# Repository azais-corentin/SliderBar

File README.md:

<p align="center">

  <h3 align="center">SliderBar</h3>

  <p align="center">
    Motorized keyboard slider with an advanced controller.
  </p>
</p>

## Table of contents

- [What's that](#whats-that)
- [Quick start](#quick-start)
- [Documentation](#documentation)
- [Copyright and license](#copyright-and-license)

## What's that

It's a keyboard slider that connects to your computer using USB.
Depending on the plugins you loaded using the desktop application, you can use your slider to execute some actions.
Here are some examples:
- Switch chrome tabs easily in one swipe.
- Switch between opened applications.
- Scroll through a window.
- Control sliders and other things in applications like Photoshop or After Effects.

## Quick start

### Get started as a user

Too early in the development for that.

### Get started with development

Follow this short guide:

- Clone the repo: `git clone --recursive https://github.com/haellsigh/SliderBar.git`
- If you want to develop for desktop:
  - Install Qt Creator with Qt > 4.0
- If you want to develop for embedded:
  - Install [PlatformIO](https://platformio.org/platformio-ide) for [VSCode](https://code.visualstudio.com/) or [Atom](https://atom.io/).

Read the [Getting started page](https://sliderbar.readthedocs.io/en/latest/) for information on the SliderBar, example plugins and more.

## Documentation

SliderBar's documentation, included in this repo in the `docs/` directory, is built
with [Sphinx](http://www.sphinx-doc.org/en/master/) and
[Doxygen](http://www.doxygen.nl/) and publicly hosted ReadTheDocs at <https://sliderbar.readthedocs.io/en/latest/>.

## Copyright and license

Code and documentation copyright 2017-2018
[Haellsigh](https://github.com/haellsigh). Code and
docs released under the [MIT
License](https://github.com/Haellsigh/SliderBar/blob/master/LICENSE).

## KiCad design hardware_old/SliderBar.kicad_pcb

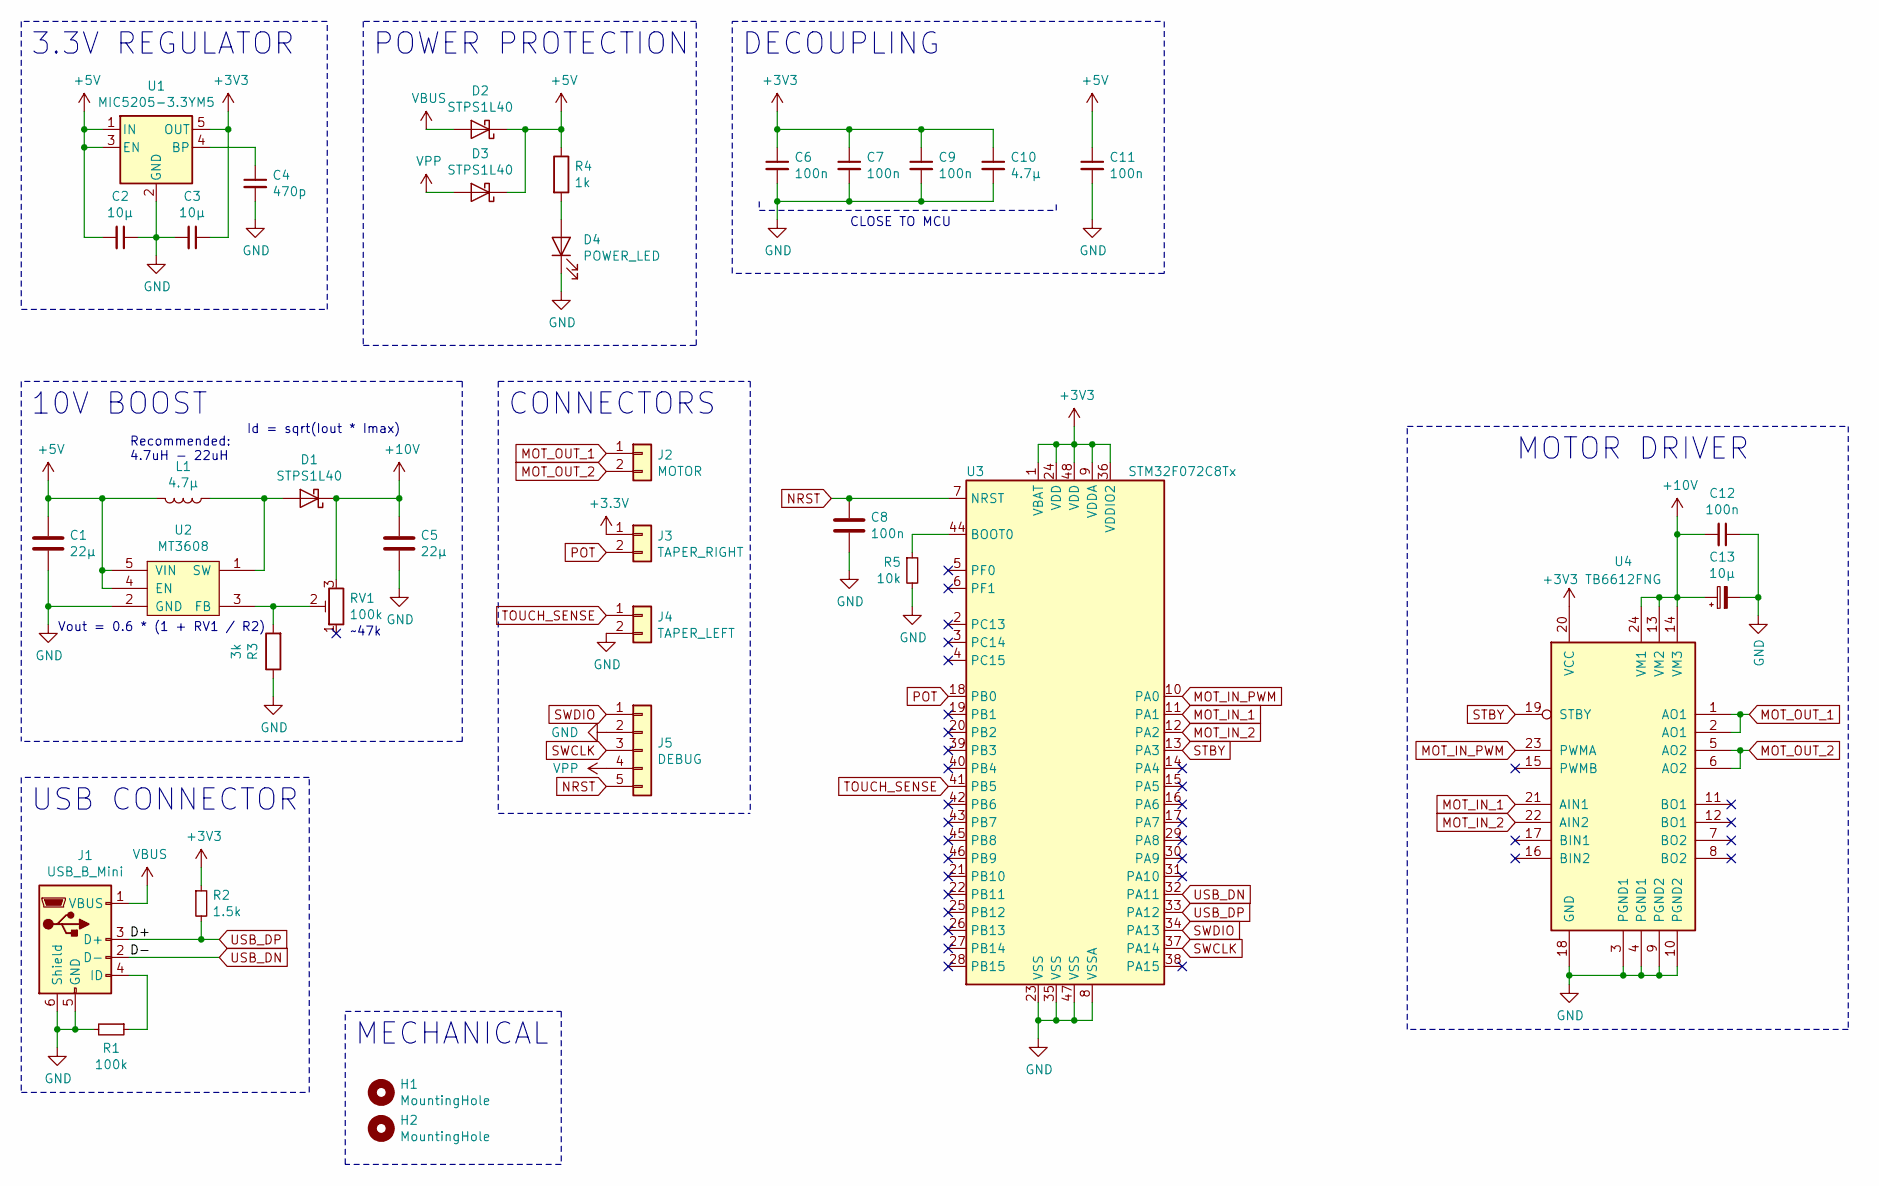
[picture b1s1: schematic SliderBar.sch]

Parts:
C1, C5: 22µ; C_0805_2012Metric_Pad1.15x1.40mm_HandSolder
C2, C3: 10µ; C_0805_2012Metric_Pad1.15x1.40mm_HandSolder
C4: 470p; C_0805_2012Metric_Pad1.15x1.40mm_HandSolder
C6, C7, C8, C9, C11, C12: 100n; C_0805_2012Metric_Pad1.15x1.40mm_HandSolder
C10: 4.7µ; C_0805_2012Metric_Pad1.15x1.40mm_HandSolder
C13: 10µ; CP_EIA-6032-28_Kemet-C_Pad2.25x2.35mm_HandSolder
D1, D2, D3: STPS1L40; D_SMA
D4: POWER_LED; LED_1206_3216Metric_Pad1.42x1.75mm_HandSolder
H1, H2: MountingHole; MountingHole_2.2mm_M2_Pad
J1: USB_B_Mini; USB_Mini-B_Lumberg_2486_01_Horizontal
J2: MOTOR; JST_GH_SM02B-GHS-TB_1x02-1MP_P1.25mm_Horizontal
J3: TAPER_RIGHT; JST_GH_SM02B-GHS-TB_1x02-1MP_P1.25mm_Horizontal
J4: TAPER_LEFT; JST_GH_SM02B-GHS-TB_1x02-1MP_P1.25mm_Horizontal
J5: DEBUG; JST_GH_BM05B-GHS-TBT_1x05-1MP_P1.25mm_Vertical
L1: 4.7µ; L_7.3x7.3_H3.5
R1: 100k; R_0805_2012Metric_Pad1.15x1.40mm_HandSolder
R2: 1.5k; R_0805_2012Metric_Pad1.15x1.40mm_HandSolder
R3: 3k; R_0805_2012Metric_Pad1.15x1.40mm_HandSolder
R4: 1k; R_0805_2012Metric_Pad1.15x1.40mm_HandSolder
R5: 10k; R_0805_2012Metric_Pad1.15x1.40mm_HandSolder
RV1: 100k; AB2_POT_TRIM
U1: MIC5205-3.3YM5; SOT-23-5
U2: MT3608; SOT-23-6_Handsoldering
U3: STM32F072C8Tx; LQFP-48_7x7mm_P0.5mm
U4: TB6612FNG; SSOP-24_5.3x8.2mm_P0.65mm

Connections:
+5V: C1.1, C2.2, C11.1, D2.1 (K), D3.1 (K), L1.2, R4.1, U1.1 (IN), U1.3 (EN), U2.4 (EN), U2.5 (VIN)
+10V: C5.2, C12.2, C13.1, D1.1 (K), RV1.3, U4.13 (VM2), U4.14 (VM3), U4.24 (VM1)
GND: C1.2, C2.1, C3.2, C4.2, C5.1, C6.2, C7.2, C8.2, C9.2, C10.2, C11.2, C12.1, C13.2, D4.1 (K), J1.5 (GND), J1.6 (Shield), J4.2, J5.2, R1.2, R3.1, R5.2, U1.2 (GND), U2.2 (GND), U3.8 (VSSA), U3.23 (VSS), U3.35 (VSS), U3.47 (VSS), U4.3 (PGND1), U4.4 (PGND1), U4.9 (PGND2), U4.10 (PGND2), U4.18 (GND)
MOT_IN_1: U3.11 (PA1), U4.21 (AIN1)
MOT_IN_2: U3.12 (PA2), U4.22 (AIN2)
MOT_IN_PWM: U3.10 (PA0), U4.23 (PWMA)
MOT_OUT_1: J2.1, U4.1 (AO1), U4.2 (AO1)
MOT_OUT_2: J2.2, U4.5 (AO2), U4.6 (AO2)
NRST: C8.1, J5.5, U3.7 (NRST)
unnamed: C4.1, U1.4 (BP)
unnamed: D1.2 (A), L1.1, U2.1 (SW)
unnamed: D4.2 (A), R4.2
unnamed: J1.4 (ID), R1.1
unnamed: R3.2, RV1.2, U2.3 (FB)
unnamed: R5.1, U3.44 (BOOT0)
POT: J3.2, U3.18 (PB0)
STBY: U3.13 (PA3), U4.19 (STBY)
SWCLK: J5.3, U3.37 (PA14)
SWDIO: J5.1, U3.34 (PA13)
TOUCH_SENSE: J4.1, U3.41 (PB5)
USB_DN: J1.2 (D-), U3.32 (PA11)
USB_DP: J1.3 (D+), R2.2, U3.33 (PA12)
VBUS: D2.2 (A), J1.1 (VBUS)
VPP: D3.2 (A), J5.4

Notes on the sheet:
3.3V REGULATOR
~~47k
10V BOOST
Id = sqrt(Iout * Imax)
Vout = 0.6 * (1 + RV1 / R2)
Recommended: 4.7uH - 22uH
POWER PROTECTION
CONNECTORS
USB CONNECTOR
MOTOR DRIVER
CLOSE TO MCU
MECHANICAL
DECOUPLING

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
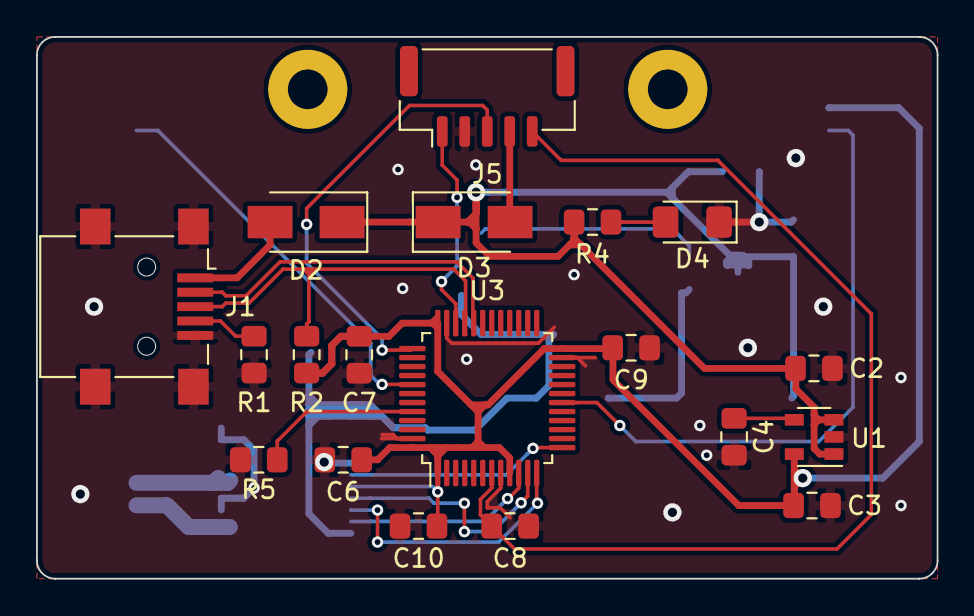
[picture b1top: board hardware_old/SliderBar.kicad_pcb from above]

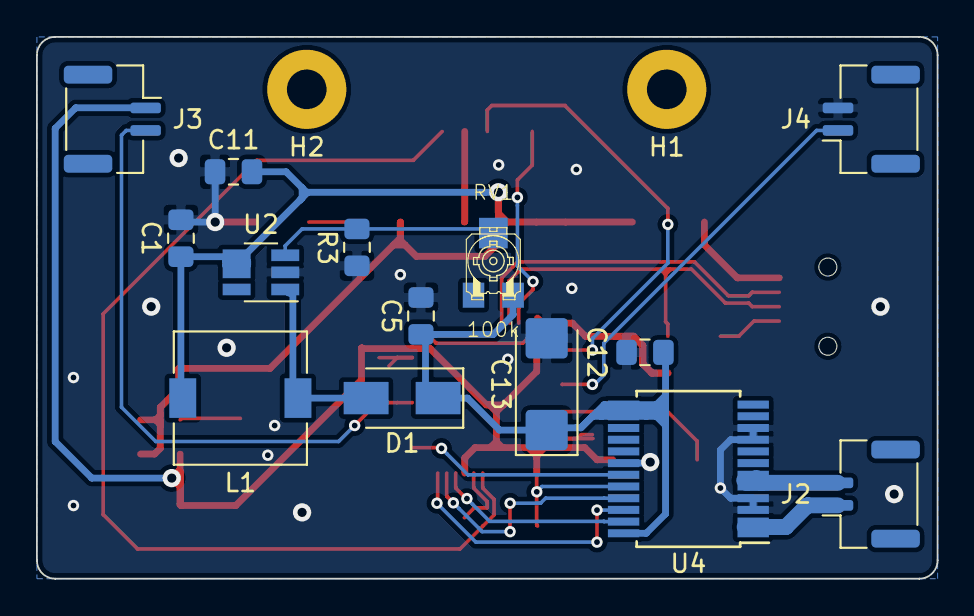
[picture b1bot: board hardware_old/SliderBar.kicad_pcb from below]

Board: 2 copper layers, 50.0 x 30.1 mm, 35 parts (16 on the bottom side), 25 nets.

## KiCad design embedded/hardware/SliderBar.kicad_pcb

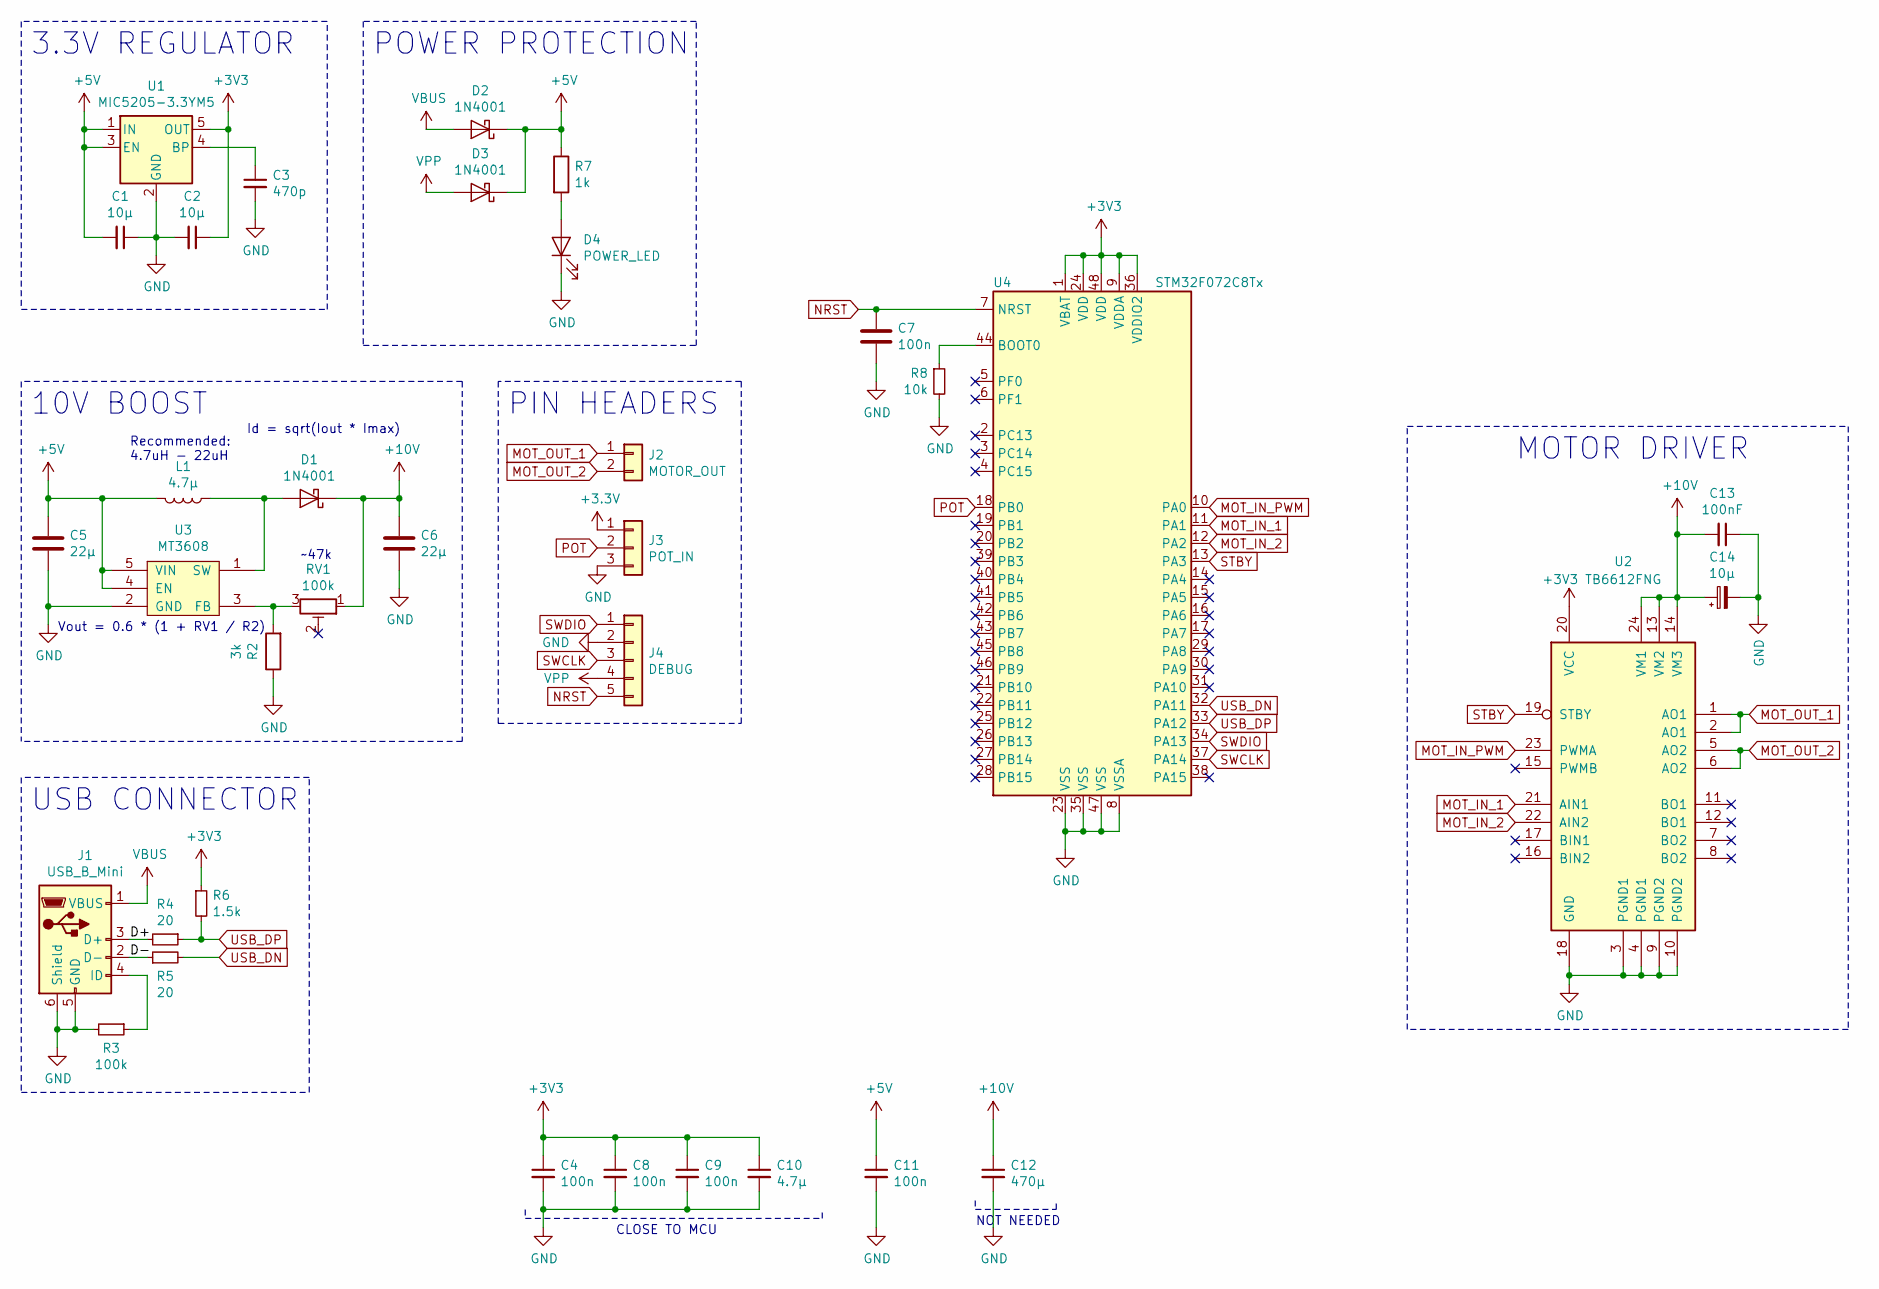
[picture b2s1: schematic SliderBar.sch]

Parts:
C1, C2: 10µ; C_1206_3216Metric_Pad1.42x1.75mm_HandSolder
C3: 470p; C_1206_3216Metric_Pad1.42x1.75mm_HandSolder
C4, C7, C8, C9, C11: 100n; C_1206_3216Metric_Pad1.42x1.75mm_HandSolder
C5, C6: 22µ; C_1206_3216Metric_Pad1.42x1.75mm_HandSolder
C10: 4.7µ; C_1206_3216Metric_Pad1.42x1.75mm_HandSolder
C12: 470µ; C_1206_3216Metric_Pad1.42x1.75mm_HandSolder
C13: 100nF; C_1206_3216Metric_Pad1.42x1.75mm_HandSolder
C14: 10µ; CP_EIA-7343-15_Kemet-W
D1, D2, D3: 1N4001; D_SMA_Handsoldering
D4: POWER_LED; LED_1206_3216Metric_Pad1.42x1.75mm_HandSolder
J1: USB_B_Mini; USB_Mini-B_Lumberg_2486_01_Horizontal
J2: MOTOR_OUT; Molex_PicoBlade_53048-0210_1x02_P1.25mm_Horizontal
J3: POT_IN; Molex_PicoBlade_53048-0310_1x03_P1.25mm_Horizontal
J4: DEBUG; Molex_PicoBlade_53047-0510_1x05_P1.25mm_Vertical
L1: 4.7µ; L_1206_3216Metric_Pad1.42x1.75mm_HandSolder
R2: 3k; R_1206_3216Metric_Pad1.42x1.75mm_HandSolder
R3: 100k; R_1206_3216Metric_Pad1.42x1.75mm_HandSolder
R4, R5: 20; R_1206_3216Metric_Pad1.42x1.75mm_HandSolder
R6: 1.5k; R_1206_3216Metric_Pad1.42x1.75mm_HandSolder
R7: 1k; R_1206_3216Metric_Pad1.42x1.75mm_HandSolder
R8: 10k; R_1206_3216Metric_Pad1.42x1.75mm_HandSolder
RV1: 100k; AB2_POT_TRIM
U1: MIC5205-3.3YM5; SOT-23-5
U2: TB6612FNG; SSOP-24_5.3x8.2mm_P0.65mm
U3: MT3608; SOT-23-6_Handsoldering
U4: STM32F072C8Tx; LQFP-48_7x7mm_P0.5mm

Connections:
+5V: C1.2, C5.1, C11.1, D2.1 (K), D3.1 (K), L1.2, R7.1, U1.1 (IN), U1.3 (EN), U3.4 (EN), U3.5 (VIN)
+10V: C6.2, C12.1, C13.2, C14.1, D1.1 (K), RV1.1, U2.13 (VM2), U2.14 (VM3), U2.24 (VM1)
/D+: J1.3 (D+), R4.2
/D-: J1.2 (D-), R5.1
GND: C1.1, C2.2, C3.2, C4.2, C5.2, C6.1, C7.2, C8.2, C9.2, C10.2, C11.2, C12.2, C13.1, C14.2, D4.1 (K), J1.5 (GND), J1.6 (Shield), J3.3, J4.2, R2.1, R3.2, R8.2, U1.2 (GND), U2.3 (PGND1), U2.4 (PGND1), U2.9 (PGND2), U2.10 (PGND2), U2.18 (GND), U3.2 (GND), U4.8 (VSSA), U4.23 (VSS), U4.35 (VSS), U4.47 (VSS)
MOT_IN_1: U2.21 (AIN1), U4.11 (PA1)
MOT_IN_2: U2.22 (AIN2), U4.12 (PA2)
MOT_IN_PWM: U2.23 (PWMA), U4.10 (PA0)
MOT_OUT_1: J2.1, U2.1 (AO1), U2.2 (AO1)
MOT_OUT_2: J2.2, U2.5 (AO2), U2.6 (AO2)
NRST: C7.1, J4.5, U4.7 (NRST)
unnamed: C3.1, U1.4 (BP)
unnamed: D1.2 (A), L1.1, U3.1 (SW)
unnamed: D4.2 (A), R7.2
unnamed: J1.4 (ID), R3.1
unnamed: R2.2, RV1.3, U3.3 (FB)
unnamed: R8.1, U4.44 (BOOT0)
POT: J3.2, U4.18 (PB0)
STBY: U2.19 (STBY), U4.13 (PA3)
SWCLK: J4.3, U4.37 (PA14)
SWDIO: J4.1, U4.34 (PA13)
USB_DN: R5.2, U4.32 (PA11)
USB_DP: R4.1, R6.2, U4.33 (PA12)
VBUS: D2.2 (A), J1.1 (VBUS)
VPP: D3.2 (A), J4.4

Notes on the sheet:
3.3V REGULATOR
~~47k
10V BOOST
Id = sqrt(Iout * Imax)
Vout = 0.6 * (1 + RV1 / R2)
Recommended: 4.7uH - 22uH
POWER PROTECTION
PIN HEADERS
USB CONNECTOR
MOTOR DRIVER
CLOSE TO MCU
NOT NEEDED

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
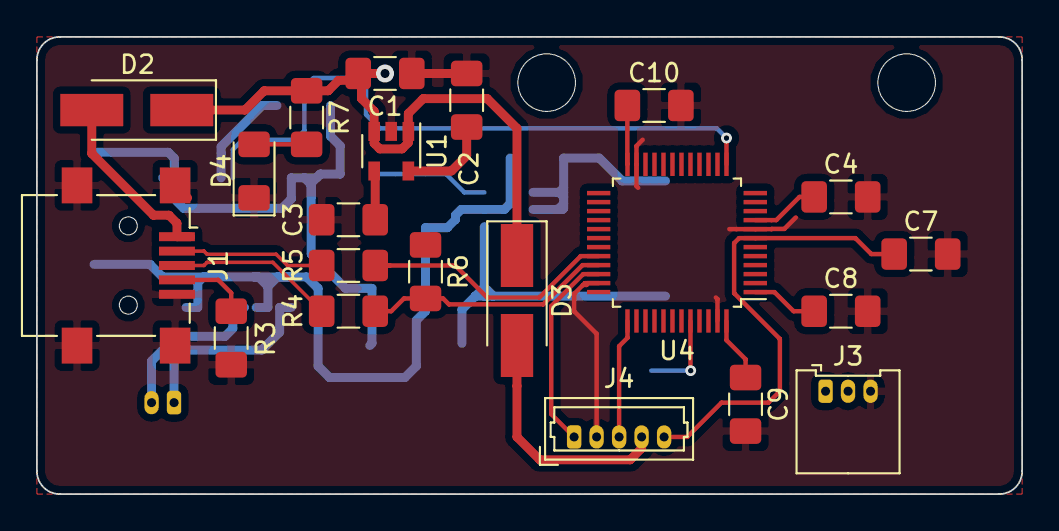
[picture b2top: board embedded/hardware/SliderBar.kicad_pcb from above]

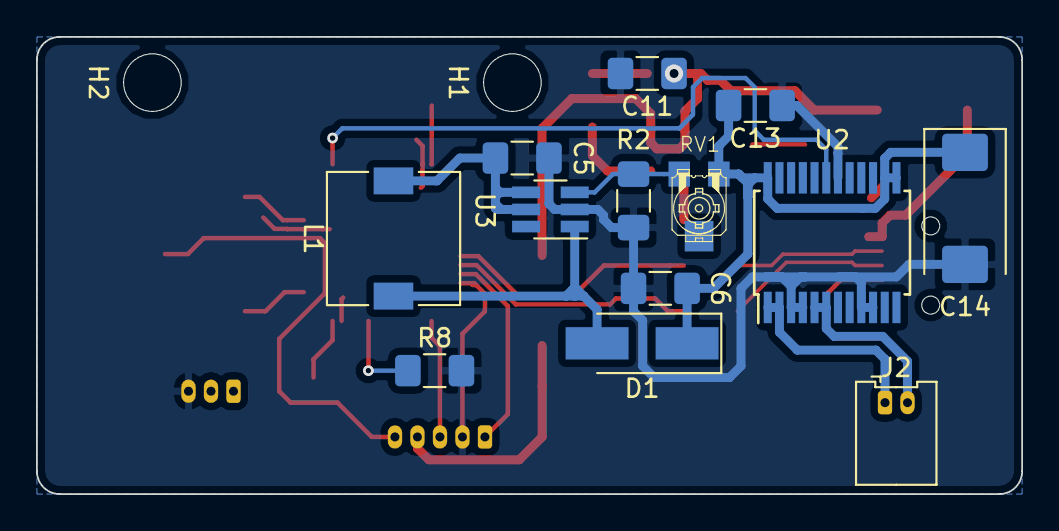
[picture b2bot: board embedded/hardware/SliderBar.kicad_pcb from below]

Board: 2 copper layers, 54.7 x 25.4 mm, 36 parts (13 on the bottom side), 26 nets.

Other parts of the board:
H1, H2: MountingHole; MountingHole_3.2mm_M3_ISO14580

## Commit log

2017-04-26 Base application
2017-04-27 Update ignore for Qt
2017-04-27 Remove user file
2017-04-27 Add SerialSettings and Settings
2017-04-27 Update ignore for build folders
2017-04-28 Separate GUI from Serial and add base protocol
2017-04-28 Working encoding and decoding of packets
2017-04-28 Add settings for protocol
2017-04-30 Define and separate components of the serial protocol
2017-05-07 Began CRC work and identified problem
2017-05-07 Update protocol
2017-05-07 Base plugin project
2017-05-07 Base Arduino project using PlatformIO on Atom
2017-05-07 Working packets sending from arduino and receiving on pc
2017-05-13 Adding CRC on Arduino & code cleanup
2017-05-14 Finished protocol
2017-05-14 Rename to SliderBar & base plugin interface
2017-05-19 Motor control on Arduino
2017-05-19 Optimize PID & Motor driver
2017-05-19 Add global keyboard hook for plugins
2017-05-21 Added ACK to protocol & prevent integral windup
2017-05-28 Move files to source folder
2017-05-28 Add PCB files
2017-06-03 Update PCB, Add resist_at basic support
2017-07-16 Improve PID Performances & Add tracking filter & graphs
2017-08-20 Add settings support and useful functions to SliderInterface
2017-08-20 Added slots and signals for plugins
2017-08-30 Fix connection
2017-10-18 Fixed comments
2018-01-15 Update for C++11
2018-01-15 Add new SlideScroll plugin
2018-01-18 Restarting circuit
2018-09-26 Deprecate all current progress
2018-09-26 Add motor driver doc
2018-10-01 Add STM32 doc
2018-10-01 Design schematic base
2018-10-03 Begin firmware
2018-10-03 Add a bit a documentation
2018-10-03 Move out of SliderBar folder
2018-10-03 Enable c++11
2018-10-14 Update NeliCadLibs
2018-10-14 Add step-up boost converter
2018-10-14 Update code
2018-10-14 Update gitignore
2018-10-17 Update schematic
2018-10-17 Change project to STM32CubeHal, move USB_CDC to lib folder
2018-10-17 Remove a shitton of useless commends
2018-10-17 Move USB_CDC to it's own class
2018-10-18 Make ErrorHandler c compatible
2018-10-18 Finish moving CDC to it's own class
2018-10-18 Removed more useless comments
2018-10-18 Remove simulation
2018-10-18 Begin TB6612FNG driver
2018-10-19 Add trimmer and replace MCU with STM32F072C8T6
2018-10-19 Add main SliderBar class
2018-10-20 Add TB6612FNG move functions
2018-10-20 Add global pointer to CDC class
2018-10-20 Formatting
2018-10-20 Adds run() loop
2018-10-21 Add variable size buffer class
2018-10-21 Begin adding simple protocol decoding
2018-10-22 Move protocol decoding features to namespace 'protocol'
2018-10-23 Change int to uint8_t
2018-10-24 Remove template from Buffer class
2018-10-24 Adapt for fixed size buffer
2018-10-24 Add CRC8 code & adapt for fixed size buffer
2018-10-25 Change Buffer containter to simple array again
2018-10-25 Change buffer to pointer, cleanup code
2018-10-25 Finish the decoding code
2018-10-25 Rename to USBCDC from USB_CDC
2018-10-25 Create the USBInterface abstract class
2018-10-25 Fix includes, separate CDC from SliderBar
2018-10-26 Change Voltage regulator to MIC5205
2018-10-29 Fix circular dependencies
2018-10-30 Fix GND rotation
2018-10-30 Add Word files
2018-10-30 Begin technical documentation
2018-10-30 Add Hardware and Software specifications
2018-10-30 Add table of contents
2018-10-30 Fixed TOC small caps
2018-10-30 Update headers & footers
2018-10-30 Add electrical characteristics, begin general description
2018-10-30 Begin hardware specs
2018-10-31 Fixed sym link & added trimpot
2018-10-31 Fix schottky diodes, finish schematic
2018-10-31 Create bare pcb
2018-10-31 Fix footprints
2018-10-31 Define board size, place USB connector
2018-10-31 Ignore backup pcb files
2018-10-31 Set clearance
2018-10-31 Rotated mcu
2018-10-31 Fix ignore
2018-10-31 Add GND to power class
2018-10-31 Replace trimpot
2018-10-31 Layout: motor driver, boost converter, 3.3v regulator, debug header, MCU, USB tracks
2018-10-31 Update pcb
2018-11-01 Change connector footprints to JST GH 1.25mm
2018-11-01 Add HTML bom
2018-11-01 Add HTML bom, again
2018-11-02 Fix lot of footprints, Add mounting holes
2018-11-04 Create base Qt project
2018-11-04 Move outside SliderBar folder, add SliderBar class
2018-11-05 Move to source folder, and hardware folder
2018-11-05 Move protocol to common folder for embedded
2018-11-07 Move Buffer to common libraries
2018-11-08 Change write/append methods, this implements issue #2
2018-11-08 Add partial support for encoding other types
2018-11-17 Temporary changes, need to update with templated version
2018-11-18 Template the buffer encoding/decoding
2018-11-18 Begin using Sphinx for doc
2018-11-18 Update theme
2018-11-18 Add the 4 doc pages
2018-11-20 Add extract and append buffer methods
2018-11-20 Update encoding and decoding
2018-11-20 Route some more traces
2018-11-21 Add nanopb to encode/decode messages, restructure some files and modify as needed
2018-11-22 Working nanopb example on embedded sideé
2018-11-22 Split DataInterface class to In and Out classes
2018-11-22 First working data exchange
2018-11-23 Defined the SliderBar communication protocol, began implementation
2018-11-23 Working actual data echange
2018-11-24 Add NACK support
2018-11-24 Add calibration to the GUI
2018-11-25 Fixed point PI controller implementation
2018-11-28 Finish FixedPointPI controller
2018-11-28 Add setCalibration request
2018-11-29 Move SliderBar settings to its own class and handle connection properly
2018-11-29 Fix functions parameters and use protocol:: structures
2018-12-01 Add restore settings confirmation & status bar info
2018-12-01 Add Nanopb as a submodule
2018-12-01 Update README with basic informations
2018-12-02 Move SliderBar related class to SliderBar namespace
2018-12-02 Rename namespace to lowercase
2019-01-21 Trying to add LUA to project
2019-01-21 Update gitignore for workspace
2019-01-21 Update nanopb
2019-01-21 Update description
2019-01-22 Move mounting holes to a schematic bloc
2019-01-22 Add 3D CAD files for Motorized Pot, SliderBar PCB, Keyboard case
2019-01-22 Assemble PCB and Potentiometer
2019-01-22 Added DECOUPLING category to schematic
2019-01-22 Add schematic pdf
2019-01-22 Add schematic svg
2019-01-23 Final schematic update for prototype
2019-01-23 Setup PCB design rules and imported footprints
2019-01-23 Fix potentiometer wiring, move Nelib library outside of project
2019-01-23 Add touch sense connection
2019-01-23 Fix capacitor valuee
2019-01-23 Add some 3D models from internet, fix some things
2019-01-24 Removed USB DP/DM resistors & Placed connectors
2019-01-24 Placed some components, fixed schematic
2019-01-25 Placed front components
2019-01-25 Placed back components
2019-01-25 Finished prototype PCB & 3D
2019-01-28 Added working example plugin base for Lua
2019-02-14 Add plugin settings & plugin setting in GUI
2019-02-15 Synchronised each plugin's settings properly
2019-02-19 No edit triggers on SettingsDialog
2019-05-26 Replace PlatformIO embedded project with CMake project with STM32CubeMX
2019-05-26 Add base project files after CubeMX generation
2019-05-27 Add CLion configuration files
2019-05-27 Restructure the project a bit
2019-05-27 Working USB CDC data transmission
2019-05-27 Copy the old SliderBar embedded class
2019-05-28 Add gitignore to the embedded project
2019-05-28 Re-add nanopb as a submodule
2019-05-28 Remove nanopb submodule
2019-05-28 Add a fixed version of nanopb
2019-06-08 Add base STM32CubeMX project with working USB comms
2019-06-08 Archive the current hardware files
2019-06-08 Remove KiCad files from .gitignore
2019-06-08 Update gitignore for KiCad
2019-06-09 Add STM32F072C8 MCU
2019-06-09 Add design notes
2019-06-09 Change schematic sheet size to A3
2019-06-09 Add ULDO 3.3V regulator
2019-06-09 Add power protection diodes
2019-06-10 Add decoupling caps
2019-06-11 Add USB connector
2019-06-11 Add motor driver with current limiting
2019-06-11 Remove units from passive components values
2019-06-11 Add current limits calculations
2019-06-18 Ignore STM32CubeMX generated files
2019-06-18 Ignore .xml files
2019-06-18 Add C wrapper for CDC class
2019-06-18 Remove generated files & add C wrapper for CDC class
2019-06-18 Formatted project
2019-06-18 Change formatting style to Chromium based
2019-09-14 Update to latest
2020-06-09 Start a fresh repository
2020-11-19 Revert "Start a fresh repository"
    This reverts commit fbaef52d0d564c90902da6cbc93ca921747f7037.
